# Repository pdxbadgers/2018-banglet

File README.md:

DEFCON 26 DC503 VIP Banglet
---------------------------
Here we are, another crazy year, another crazy party badge.  Necks are so over-used, so this year we're migrating to the wrist.  The idea is a fully functional bluetooth recon device with multiple, um, "hidden" party modes on the bleuart (like, UART over bluetooth, crazy right?) service.

credits (github/twitter)
------------------------

Original Concept:
* @nishakm / @nishakmr

Board Design:
* @nishakm / @nishakmr
* @r00tkillah

3D Design:
* @jonhannis
* @pierce403 / @deanpierce

PCB necromancers:
* @r00tkillah
* @securelyfitz
* @office_deskjet
* @nishakm / @nishakmr
* @jonhannis

Code monkeys:
* @pierce403 / @deanpierce
* @nishakm / @nishakmr

Special thanks to Adafruit Industries for publishing their board designs, 3D designs and NRF52 Arduino code examples.

And a special thanks to everyone else who donated time, money, or crazy ideas that helped make this possible.

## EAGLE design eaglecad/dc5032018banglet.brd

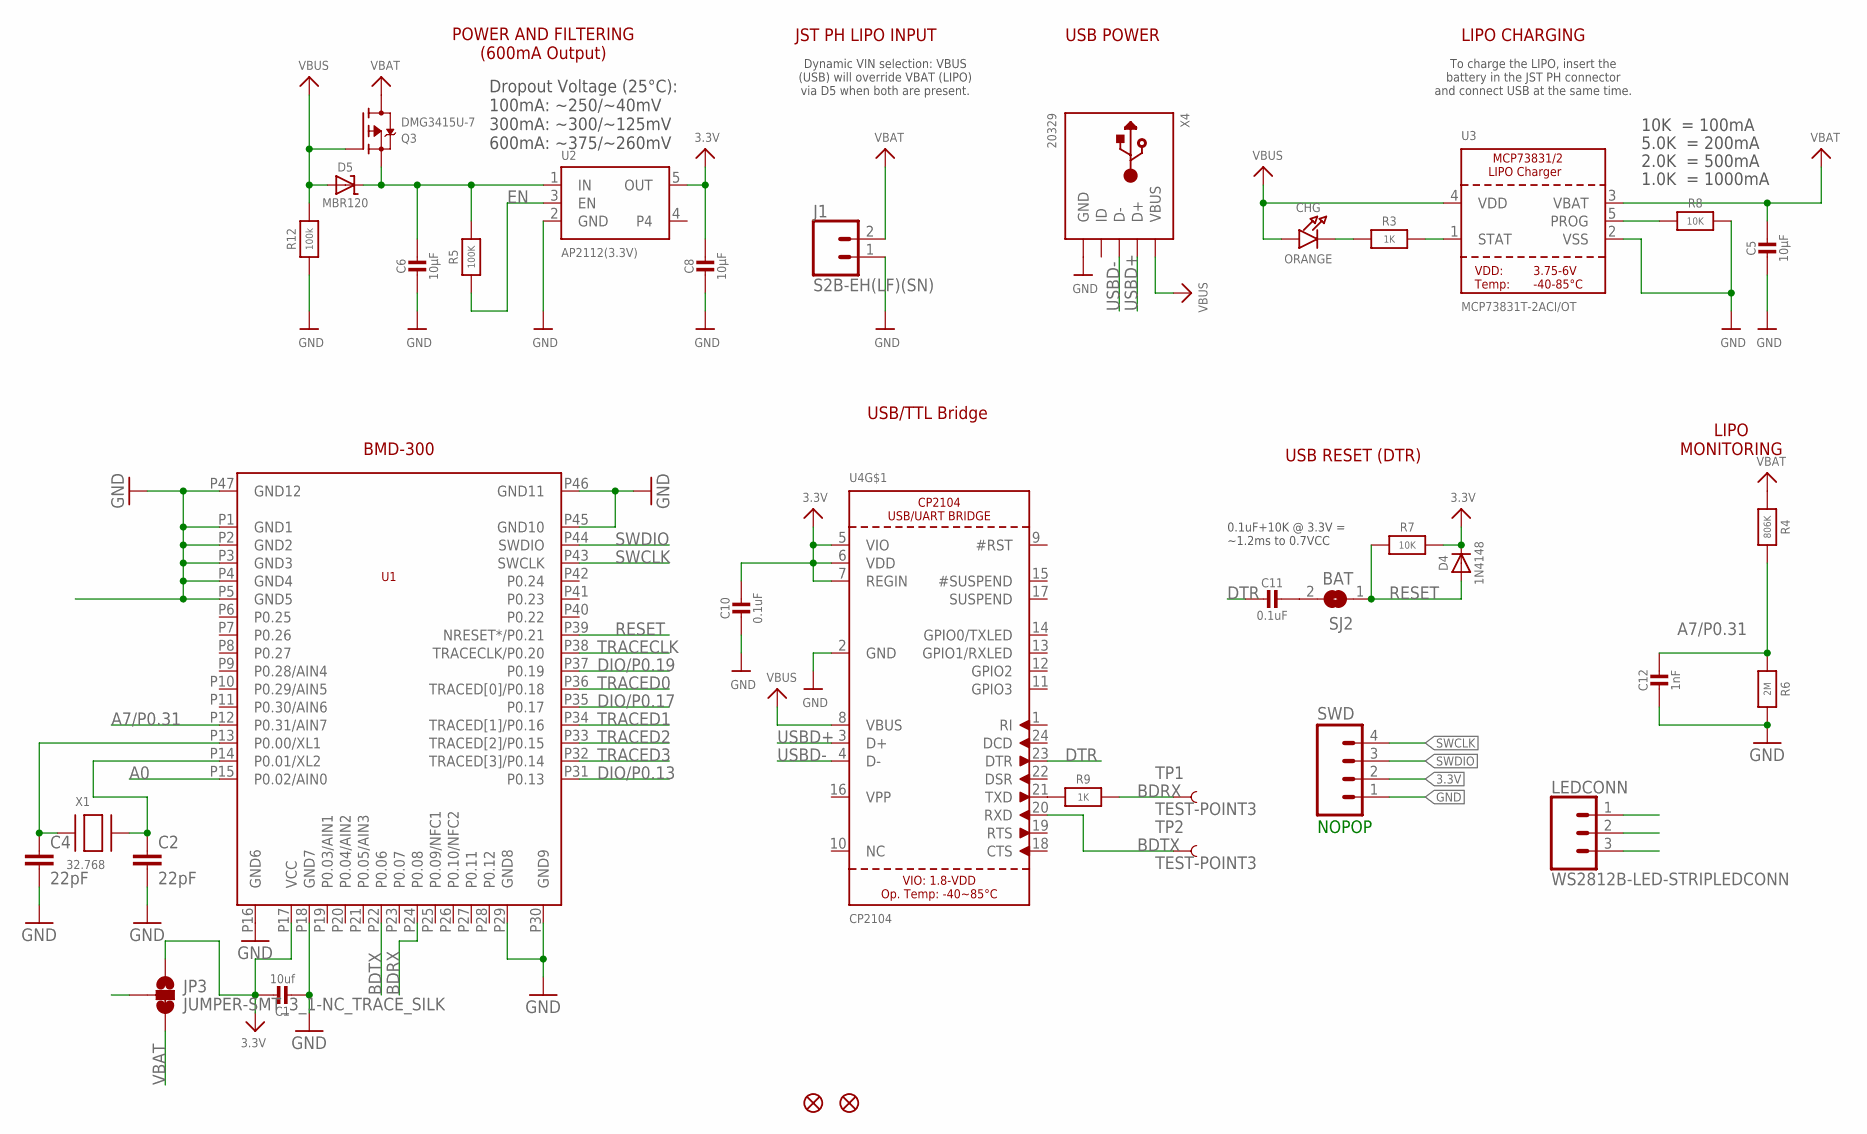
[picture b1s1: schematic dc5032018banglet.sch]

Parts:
C1: 10uf; 0805-NO
C2, C4: 22pF; 0603
C5, C6, C8: 10µF; 0805-NO
C10, C11: 0.1uF; 0603-NO
C12: 1nF; 0603-NO
CHG: ORANGE; CHIPLED_0805_NOOUTLINE
D4: 1N4148; SOD-323
D5: MBR120; SOD-123
FD1, FD2: FIDUCIALUFIDUCIAL; FIDUCIAL-MICRO
J1: S2B-EH(LF)(SN); 1X2(2.5)
JP3: JUMPER-SMT_3_1-NC_TRACE_SILK; SMT-JUMPER_3_1-NC_TRACE_SILK
LEDCONN: WS2812B-LED-STRIPLEDCONN; 1X3(2.5)
Q3: DMG3415U-7; SOT23-R
R3, R9: 1K; 0603-NO
R4: 806K; 0603-NO
R5: 100K; 0603-NO
R6: 2M; 0603-NO
R7, R8: 10K; 0603-NO
R12: 100k; 0603-NO
SJ2: BAT; SOLDERJUMPER_CLOSEDWIRE
SWD: M04LOCK; 1X04_LOCK@1
TP1, TP2: TEST-POINT3; PAD.03X.03
U1: BMD-300
U2: AP2112(3.3V); SOT23-5
U3: MCP73831T-2ACI/OT; SOT23-5
U4: CP2104; QFN24_4MM_SMSC
X1: 32.768; XTAL3215
X4: 20329; MICRO-USB5+6P-SMD-0.65-B

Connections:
3.3V: C1.1, C8.1, C10.1, D4.C, JP3.1, R7.2, SWD.2, U1.P17 (VCC), U2.5 (OUT), U4.5 (VIO), U4.6 (VDD), U4.7 (REGIN)
A0: LEDCONN.2, U1.P15 (P0.02/AIN0)
A7/P0.31: C12.1, R4.2, R6.1, U1.P12 (P0.31/AIN7)
BDRX: R9.2, TP1.P$1, U1.P24 (P0.08)
BDTX: TP2.P$1, U1.P22 (P0.06), U4.20 (RXD)
DIO/P0.13: U1.P31 (P0.13)
DIO/P0.17: U1.P35 (P0.17)
DIO/P0.19: U1.P37 (P0.19)
DTR: C11.2, U4.23 (DTR)
EN: R5.1, U2.3 (EN)
GND: C1.2, C2.2, C4.2, C5.2, C6.2, C8.2, C10.2, C12.2, J1.1, LEDCONN.3, R6.2, R8.2, R12.1, SWD.1, U1.P1 (GND1), U1.P2 (GND2), U1.P3 (GND3), U1.P4 (GND4), U1.P5 (GND5), U1.P16 (GND6), U1.P18 (GND7), U1.P29 (GND8), U1.P30 (GND9), U1.P45 (GND10), U1.P46 (GND11), U1.P47 (GND12), U2.2 (GND), U3.2 (VSS), U4.2 (GND), X4.5 (GND), X4.S1 (GND), X4.S2 (GND), X4.S3 (GND), X4.S4 (GND), X4.S5 (GND), X4.S6 (GND)
unnamed: C2.1, U1.P14 (P0.01/XL2), X1.P$2
unnamed: C4.1, U1.P13 (P0.00/XL1), X1.P$1
unnamed: CHG.C, R3.1
unnamed: R3.2, U3.1 (STAT)
unnamed: R8.1, U3.5 (PROG)
unnamed: R9.1, U4.21 (TXD)
unnamed: C11.1, SJ2.2
RESET: D4.A, R7.1, SJ2.1, U1.P39 (NRESET*/P0.21)
SWCLK: SWD.4, U1.P43 (SWCLK)
SWDIO: SWD.3, U1.P44 (SWDIO)
TP: U4.THERM (TP)
TRACECLK: U1.P38 (TRACECLK/P0.20)
TRACED0: U1.P36 (TRACED[0]/P0.18)
TRACED1: U1.P34 (TRACED[1]/P0.16)
TRACED2: U1.P33 (TRACED[2]/P0.15)
TRACED3: U1.P32 (TRACED[3]/P0.14)
USBD+: U4.3 (D+), X4.3 (D+)
USBD-: U4.4 (D-), X4.2 (D-)
VBAT: C5.1, J1.2, JP3.3, Q3.3 (D), R4.1, U3.3 (VBAT)
VBUS: CHG.A, D5.A, Q3.1 (G), R12.2, U3.4 (VDD), U4.8 (VBUS), X4.1 (VBUS)
VIN: C6.1, D5.C, Q3.2 (S), R5.2, U2.1 (IN)
VLED: JP3.2, LEDCONN.1

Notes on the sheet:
POWER AND FILTERING (600mA Output)
Dropout Voltage (25°C): 100mA: ~250/~40mV 300mA: ~300/~125mV 600mA: ~375/~260mV
JST PH LIPO INPUT
Dynamic VIN selection: VBUS (USB) will override VBAT (LIPO) via D5 when both are present.
USB POWER
10K = 100mA
5.0K = 200mA
2.0K = 500mA
1.0K = 1000mA
LIPO CHARGING
To charge the LIPO, insert the battery in the JST PH connector and connect USB at the same time.
LIPO MONITORING
USB RESET (DTR)
0.1uF+10K @ 3.3V = ~1.2ms to 0.7VCC
USB/TTL Bridge
NOPOP
BMD-300

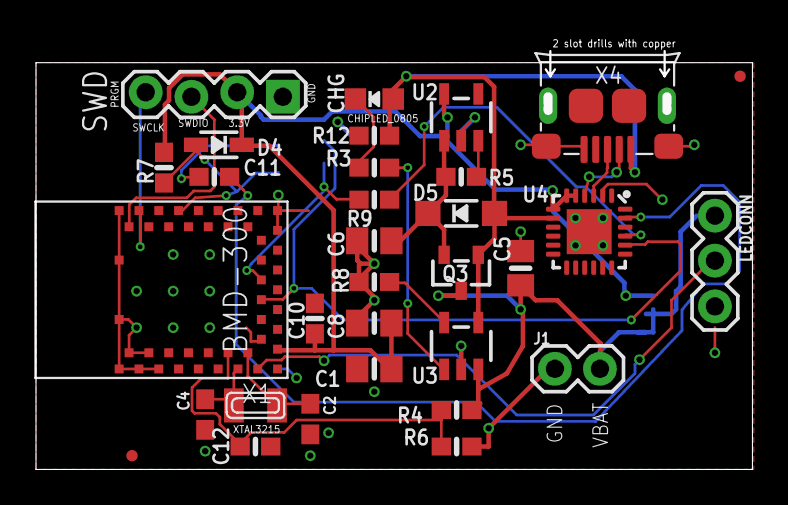
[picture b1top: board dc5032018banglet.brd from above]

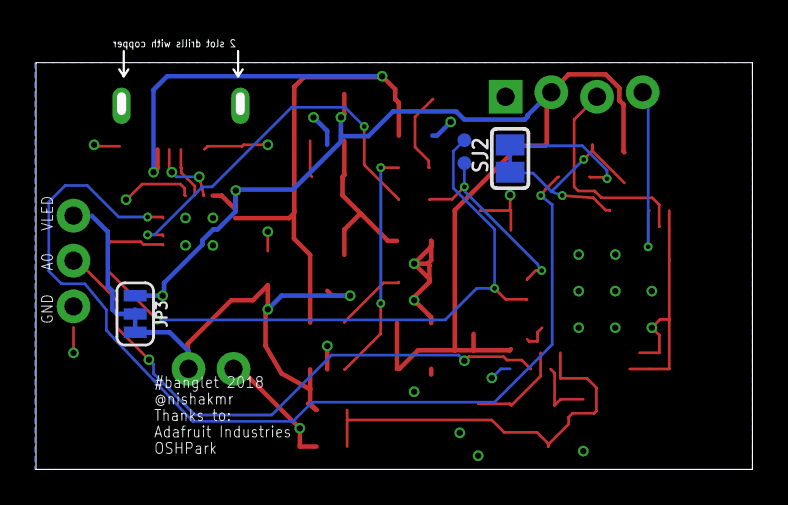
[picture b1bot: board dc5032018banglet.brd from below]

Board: 2 copper layers, 39.3 x 23.6 mm, 36 parts (4 on the bottom side), 24 nets.

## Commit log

2018-07-21 btmonitor - fun example
2018-07-21 uploading RGB BLEPerf example
2018-07-21 Added board files and color picker sketch
    Also moved btmonitor.ino to a folder because arduino IDE wants it
    there
2018-07-22 create sketches directory
2018-07-22 basic board instructions
2018-07-22 formatting
2018-07-22 add neo pixel info
2018-07-22 Moved sketches to sketches folder
2018-07-22 Central and Peripheral mode
    The central mode is in a loop and the periperal mode works on the
    remaining pixels because that responds only to callbacks from a
    central that connects and sends to it
2018-07-22 rename
2018-07-22 make STL directory
2018-07-22 add rubbery banglet
2018-07-22 added the hard banglet
2018-07-22 renaming some 3d print stuff
2018-07-22 more readme stuff
2018-07-22 more readme updates
2018-07-22 even more updates
2018-07-22 more fixups
2018-07-22 welcome to the party
2018-07-22 special thanks
2018-07-26 scanning, blinking, and shells!
2018-07-26 Added bluart interaction sketch
    Also moved patriot.ino into patriot folder so arduino won't
    yell
2018-07-26 Can now list, patriot, rainbow and off
    Also moved the lonely sketch to the arduino likey folder.
    Rainbow needs some work
2018-07-27 Renamed banglet to dual_mode
    This isn't the main sketch
2018-07-27 Added definitive banglet sketch
2018-07-27 Everyone pitched in everywhere
    Yay team! Edit if not giving credit or improper credit dueing
2018-07-28 some buffer cleaning
2018-07-28 transitioned to static buffers, fixed dumb find_mac bug
2018-07-28 More info about banglet programming
2018-07-28 Tweeks: send UART messages 28 bytes at a time
2018-07-28 make it so device names don't go away
2018-07-29 Added banglet name maker
    Until somebody can come up with a sane way of uniquely identifying
    a banglet, it'll have to resemble "Benedict Cumberbatch"
2018-07-29 some broken code for the world to look at
2018-07-29 mem management overhaul, tweaked btscan display
2018-07-29 added "list" and "count" commands
2018-07-29 there is a better way now, deleting broken code
2018-07-29 set unique bluetooth name
2018-07-30 16 bits should be enough for anyone
2018-07-30 Added init lights
2018-07-30 Added listing device names
2018-07-30 Modified RX buffer reading and parsing
2018-07-30 Modified BT scan buffers and printing
2018-07-30 Added frozen command
2018-07-30 Added listing number of devices logged
2018-07-30 Replaced Sherlock name with PDXish street names
2018-07-30 Increasing LED number to 12
2018-07-30 Seed with unique ID
2018-08-01 updated some street names
2018-08-01 switch commands to array of String objects
2018-08-01 whitespace
2018-08-01 Fixed devices and counts command printing in a loop
2018-08-01 cleaned up command parsing a bit, switched to root shell
2018-08-01 add some brightness commands
2018-08-01 separated out the concept of modes
2018-08-01 rearranged help, added fire, some game stuff
2018-08-01 whitespace
    To stop living like a heathen and use a real editor,
    file->preferences->use external editor. Then edit with your OneTrueTextEditor.
2018-08-01 Tweeked messages for unlocking levels
2018-08-01 Off for free and include rainbow mode in game
2018-08-01 add watchdog timer library
2018-08-01 added watchdog code
2018-08-01 uploading CRC headers
2018-08-01 fixed seeding by seeding with crc32 of unique ID
2018-08-02 cleaned up some serial output
2018-08-02 text style alignment
2018-08-02 updated documentation

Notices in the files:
parts and their libraries:
microbuilder: This work is placed in the public domain, and may be freely used for commercial and non-commercial work with the following conditions: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
SparkFun-Connectors: Licensing: Creative Commons ShareAlike 4.0 International - https://creativecommons.org/licenses/by-sa/4.0
